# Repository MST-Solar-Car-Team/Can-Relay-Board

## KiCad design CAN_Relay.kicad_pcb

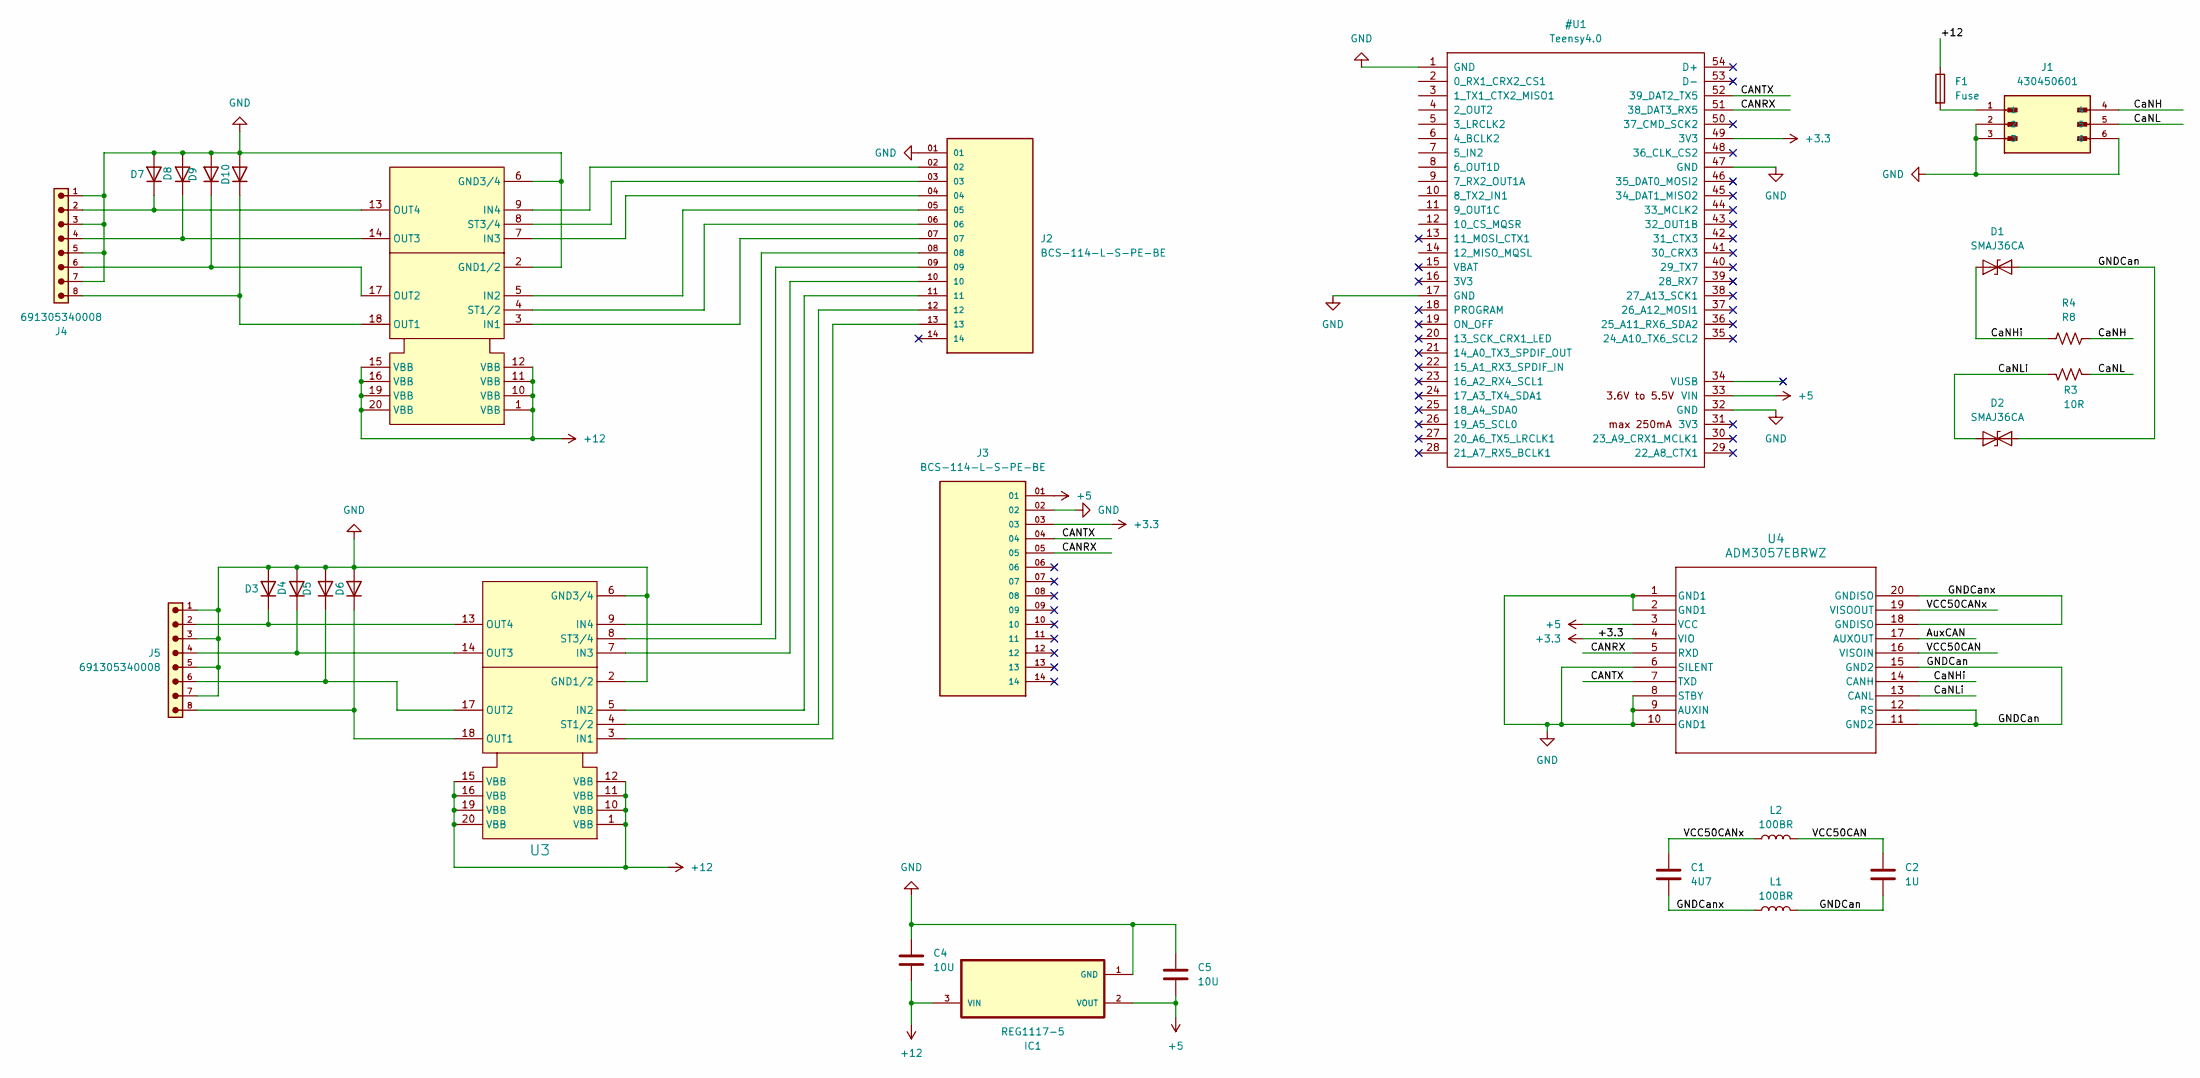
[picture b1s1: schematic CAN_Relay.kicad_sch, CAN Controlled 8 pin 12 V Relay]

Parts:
C1: 4U7; CAPC1608X95N
C2: 1U; CAPC1005X55N
C4, C5: 10U; CAPC2012X145N
D1, D2: SMAJ36CA; SMASERIES-M
D3, D4, D5, D6, D7, D8, D9, D10: D; DIO_RRE02VSM_ROM
F1: Fuse; FUSC3215X83N
IC1: REG1117-5; SOT230P700X180-4N
J1: 430450601; MOLEX_430450601; PARTREV G
J2, J3: BCS-114-L-S-PE-BE; SAMTEC_BCS-114-L-S-PE-BE; PARTREV R
J4, J5: 691305340008
L1, L2: 100BR; RESC3015X65N
R3: 10R; R_0603_1608Metric
R4: R8; R_0603_1608Metric
U2, U3: BTS716GB; SOIC127P1032X265-20N; ManufacturerPartNumber BTS716GB
U4: ADM3057EBRWZ; SOIC127P1032X265-20N

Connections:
+12: C4.2, F1.1, IC1.3 (VIN), U2.1 (VBB), U2.10 (VBB), U2.11 (VBB), U2.12 (VBB), U2.15 (VBB), U2.16 (VBB), U2.19 (VBB), U2.20 (VBB), U3.1 (VBB), U3.10 (VBB), U3.11 (VBB), U3.12 (VBB), U3.15 (VBB), U3.16 (VBB), U3.19 (VBB), U3.20 (VBB)
/AuxCAN: U4.17 (AUXOUT)
/CaNH: J1.4, R4.2
/CaNHi: D1.1 (A1), R4.1, U4.14 (CANH)
/CaNL: J1.5, R3.2
/CaNLi: D2.1 (A1), R3.1, U4.13 (CANL)
/GNDCan: C2.2, D1.2 (A2), D2.2 (A2), L1.2, U4.11 (GND2), U4.12 (RS), U4.15 (GND2)
/GNDCanx: C1.2, L1.1, U4.18 (GNDISO), U4.20 (GNDISO)
/VCC50CAN: C2.1, L2.2, U4.16 (VISOIN)
/VCC50CANx: C1.1, L2.1, U4.19 (VISOOUT)
unnamed: D3.1 (K), J5.2, U3.13 (OUT4)
unnamed: D4.1 (K), J5.4, U3.14 (OUT3)
unnamed: D5.1 (K), J5.6, U3.17 (OUT2)
unnamed: D6.1 (K), J5.8, U3.18 (OUT1)
unnamed: D7.1 (K), J4.2, U2.13 (OUT4)
unnamed: D8.1 (K), J4.4, U2.14 (OUT3)
unnamed: D9.1 (K), J4.6, U2.17 (OUT2)
unnamed: D10.1 (K), J4.8, U2.18 (OUT1)
unnamed: F1.2, J1.1
unnamed: J2.07, U2.3 (IN1)
unnamed: J2.05, U2.5 (IN2)
unnamed: J2.04, U2.7 (IN3)
unnamed: J2.02, U2.9 (IN4)
unnamed: J2.06, U2.4 (ST1/2)
unnamed: J2.03, U2.8 (ST3/4)
unnamed: J2.13, U3.3 (IN1)
unnamed: J2.11, U3.5 (IN2)
unnamed: J2.10, U3.7 (IN3)
unnamed: J2.08, U3.9 (IN4)
unnamed: J2.12, U3.4 (ST1/2)
unnamed: J2.09, U3.8 (ST3/4)

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
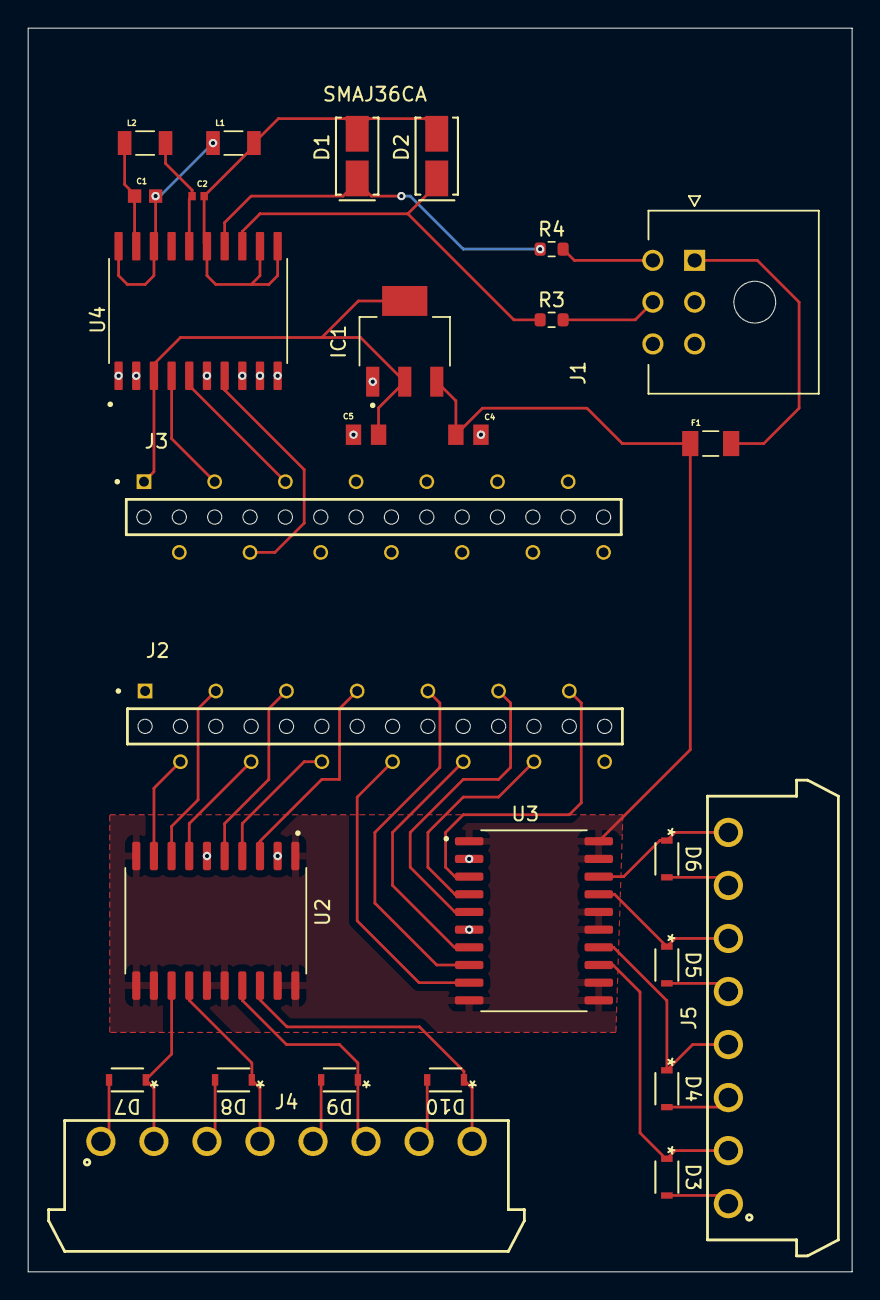
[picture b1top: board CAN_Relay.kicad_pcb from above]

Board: 2 copper layers, 59.2 x 89.4 mm, 28 parts (0 on the bottom side), 35 nets.

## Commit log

2025-08-28 Uploaded already made files and components
2025-08-29 added smd pins for teensy
2025-08-29 wired all but relay outputs
2025-08-29 Complete with Errors
2025-09-02 fixed trace not being ground
2025-09-05 experimented with ground and power planes
2025-09-10 No errors, but I hate the PCB layout
2025-09-12 Redid CAN side of PCB to replace Buck Converter
2025-09-13 Connected everything, need to set trace size
2025-09-17 Redid layout to make board more compact
2025-09-18 Added all the .step files to footprints
